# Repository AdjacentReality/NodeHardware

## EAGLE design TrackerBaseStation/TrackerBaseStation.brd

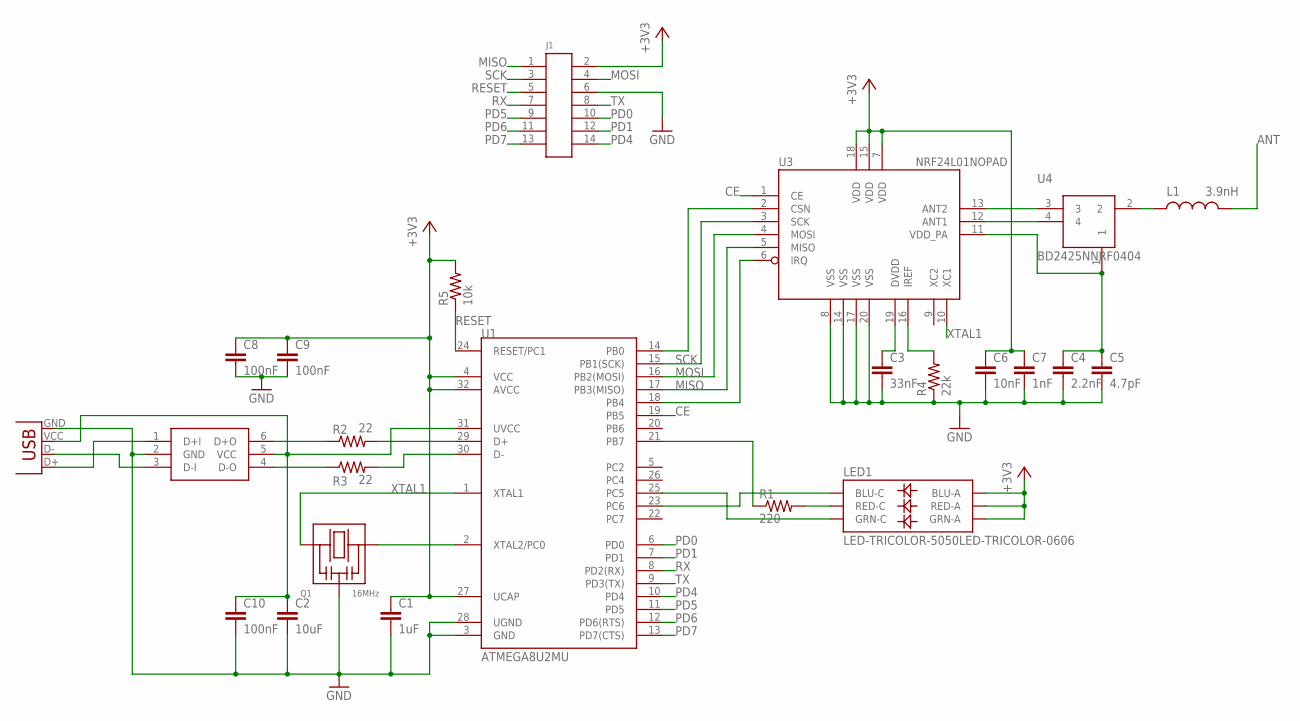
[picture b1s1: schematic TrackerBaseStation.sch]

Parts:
C1: 1uF; 0402-CAP
C2: 10uF; 0603-CAP
C3: 33nF; 0402-CAP
C4: 2.2nF; 0402-CAP
C5: 4.7pF; 0402-CAP
C6: 10nF; 0402-CAP
C7: 1nF; 0402-CAP
C8, C9, C10: 100nF; 0402-CAP
J1: DF12A3.0-14DS
L1: 3.9nH; C0402
LED1: LED-TRICOLOR-5050LED-TRICOLOR-0606; 0606
Q1: 16MHz; PRQC
R1: 220; 0402-RES
R2, R3: 22; 0402-RES
R4: 22k; 0402-RES
R5: 10k; 0402-RES
U1: ATMEGA8U2MU; QFN32
U2: RCLAMP0502A; SOT-666
U3: NRF24L01NOPAD; QFN20-NOPAD
U4: BD2425NNRF0404; BD2425NNRF
X1: USB-LEG; USB-A-SMD-LEG

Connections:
+3V3: C1.1, C6.1, C7.1, C8.1, C9.1, J1.2, LED1.4 (BLU-A), LED1.5 (RED-A), LED1.6 (GRN-A), R5.2, U1.4 (VCC), U1.27 (UCAP), U1.32 (AVCC), U3.7 (VDD), U3.15 (VDD), U3.18 (VDD)
ANT: L1.2
CE: U1.19 (PB5), U3.1 (CE)
GND: C1.2, C2.2, C3.2, C4.2, C5.2, C6.2, C7.2, C8.2, C9.2, C10.2, J1.6, Q1.P$2 (GND), R4.1, U1.3 (GND), U1.28 (UGND), U2.2 (GND), U3.8 (VSS), U3.14 (VSS), U3.17 (VSS), U3.20 (VSS), X1.GND
MISO: J1.1, U1.17 (PB3(MISO)), U3.5 (MISO)
MOSI: J1.4, U1.16 (PB2(MOSI)), U3.4 (MOSI)
unnamed: LED1.1 (BLU-C), U1.23 (PC6)
unnamed: LED1.2 (RED-C), R1.2
unnamed: R1.1, U1.21 (PB7)
unnamed: LED1.3 (GRN-C), U1.25 (PC5)
unnamed: Q1.P$3 (2), U1.2 (XTAL2/PC0)
unnamed: U2.3 (D-I), X1.D-
unnamed: U2.1 (D+I), X1.D+
unnamed: U1.14 (PB0), U3.2 (CSN)
unnamed: R2.1, U2.6 (D+O)
unnamed: R2.2, U1.29 (D+)
unnamed: R3.1, U2.4 (D-O)
unnamed: R3.2, U1.30 (D-)
unnamed: C2.1, C10.1, U1.31 (UVCC), U2.5 (VCC), X1.VCC (VBUS)
unnamed: U1.18 (PB4), U3.6 (IRQ)
unnamed: C3.1, U3.19 (DVDD)
unnamed: R4.2, U3.16 (IREF)
unnamed: U3.13 (ANT2), U4.3
unnamed: U3.12 (ANT1), U4.4
unnamed: L1.1, U4.2
unnamed: C4.1, C5.1, U3.11 (VDD_PA), U4.1
PD0: J1.10, U1.6 (PD0)
PD1: J1.12, U1.7 (PD1)
PD4: J1.14, U1.10 (PD4)
PD5: J1.9, U1.11 (PD5)
PD6: J1.11, U1.12 (PD6(RTS))
PD7: J1.13, U1.13 (PD7(CTS))
RESET: J1.5, R5.1, U1.24 (RESET/PC1)
RX: J1.7, U1.8 (PD2(RX))
SCK: J1.3, U1.15 (PB1(SCK)), U3.3 (SCK)
TX: J1.8, U1.9 (PD3(TX))
XTAL1: Q1.P$1 (1), U1.1 (XTAL1), U3.10 (XC1)

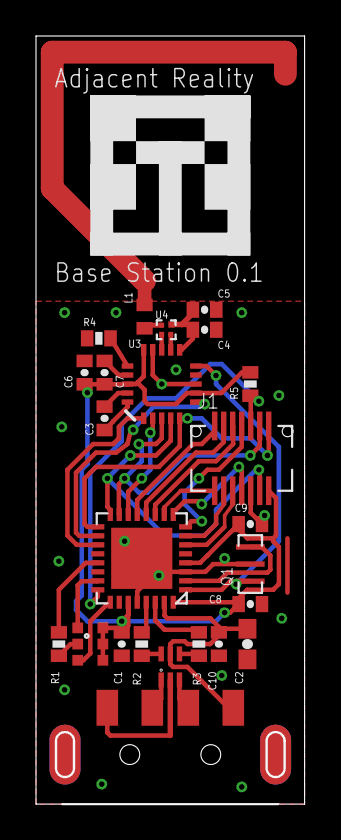
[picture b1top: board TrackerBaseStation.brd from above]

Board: 2 copper layers, 14.8 x 42.5 mm, 26 parts (1 on the bottom side), 36 nets.

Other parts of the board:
U$1: ADJACENTREALITY-LOGO-0.35
U$2: OSHW-LOGO-M

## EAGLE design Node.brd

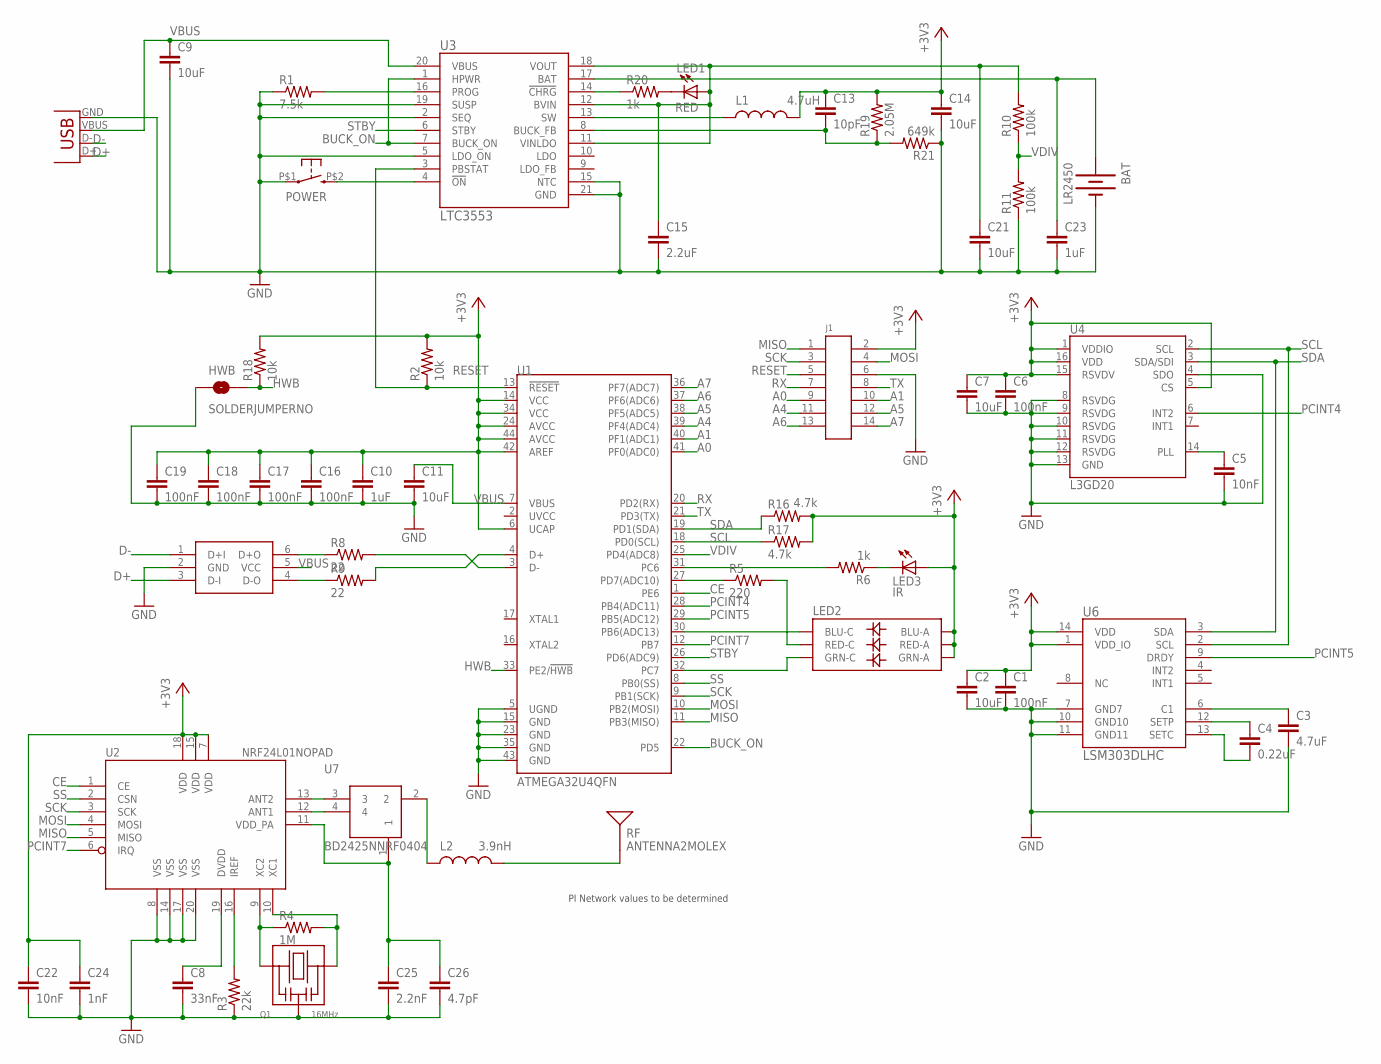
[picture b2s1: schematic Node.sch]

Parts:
BAT: LR2450; BATTCON_245MM_SLOT
C1, C6, C16, C17, C18, C19: 100nF; 0402-CAP
C2, C7, C9, C11, C14, C21: 10uF; 0603-CAP
C3: 4.7uF; 0603-CAP
C4: 0.22uF; 0402-CAP
C5, C22: 10nF; 0402-CAP
C8: 33nF; 0402-CAP
C10, C23: 1uF; 0402-CAP
C13: 10pF; 0402-CAP
C15: 2.2uF; 0402-CAP
C24: 1nF; 0402-CAP
C25: 2.2nF; 0402-CAP
C26: 4.7pF; 0402-CAP
HWB: SOLDERJUMPERNO; SJ_2S-NO
J1: DF12A3.0-14DS
L1: 4.7uH; VLS30
L2: 3.9nH; C0402
LED1: RED; LED-0603
LED2: LED-TRICOLOR-5050LED-TRICOLOR-0606; 0606
LED3: IR; LED-0603
POWER: KSS
Q1: 16MHz; PRQC
R1: 7.5k; 0402-RES
R2, R18: 10k; 0402-RES
R3: 22k; 0402-RES
R4: 1M; 0402-RES
R5: 220; 0402-RES
R6, R20: 1k; 0402-RES
R8, R9: 22; 0402-RES
R10, R11: 100k; 0402-RES
R16, R17: 4.7k; 0402-RES
R19: 2.05M; 0402-RES
R21: 649k; 0402-RES
RF: ANTENNA2MOLEX; MOLEX2.4SMD
U1: ATMEGA32U4QFN; QFN-44
U2: NRF24L01NOPAD; QFN20-NOPAD
U3: LTC3553; QFN20-3X3
U4: L3GD20; LGA16-4X4
U6: LSM303DLHC; LGA14-3X5
U7: BD2425NNRF0404; BD2425NNRF
U9: RCLAMP0502A; SOT-666
X1: USB-FCI; USB-MICROB-FCI

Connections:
+3V3: C1.1, C2.1, C6.1, C7.1, C10.1, C13.1, C14.1, C16.1, C17.1, C18.1, C19.1, C22.1, C24.1, J1.2, L1.2, LED2.4 (BLU-A), LED2.5 (RED-A), LED2.6 (GRN-A), LED3.A, R2.2, R16.2, R17.2, R18.2, R19.2, U1.6 (UCAP), U1.14 (VCC), U1.24 (AVCC), U1.34 (VCC), U1.42 (AREF), U1.44 (AVCC), U2.7 (VDD), U2.15 (VDD), U2.18 (VDD), U4.1 (VDDIO), U4.5 (CS), U4.15 (RSVDV), U4.16 (VDD), U6.1 (VDD_IO), U6.14 (VDD)
A0: J1.9, U1.41 (PF0(ADC0))
A1: J1.10, U1.40 (PF1(ADC1))
A4: J1.11, U1.39 (PF4(ADC4))
A5: J1.12, U1.38 (PF5(ADC5))
A6: J1.13, U1.37 (PF6(ADC6))
A7: J1.14, U1.36 (PF7(ADC7))
BUCK_ON: U1.22 (PD5), U3.1 (HPWR), U3.7 (BUCK_ON)
CE: U1.1 (PE6), U2.1 (CE)
D+: U9.3 (D-I), X1.D+
D-: U9.1 (D+I), X1.D-
GND: BAT.GND (-), C1.2, C2.2, C3.2, C5.2, C6.2, C7.2, C8.2, C9.2, C10.2, C11.2, C14.2, C15.2, C16.2, C17.2, C18.2, C19.2, C21.2, C22.2, C23.2, C24.2, C25.2, C26.2, HWB.1, J1.6, POWER.P$1 (1), Q1.P$2 (GND), R1.1, R3.1, R11.1, R21.1, U1.5 (UGND), U1.15 (GND), U1.23 (GND), U1.35 (GND), U1.43 (GND), U2.8 (VSS), U2.14 (VSS), U2.17 (VSS), U2.20 (VSS), U3.2 (SEQ), U3.5 (LDO_ON), U3.15 (NTC), U3.19 (SUSP), U3.21 (GND), U4.4 (SDO), U4.8 (RSVDG), U4.9 (RSVDG), U4.10 (RSVDG), U4.11 (RSVDG), U4.12 (RSVDG), U4.13 (GND), U6.7 (GND7), U6.10 (GND10), U6.11 (GND11), U9.2 (GND), X1.GND
HWB: HWB.2, R18.1, U1.33 (PE2/!HWB)
MISO: J1.1, U1.11 (PB3(MISO)), U2.5 (MISO)
MOSI: J1.4, U1.10 (PB2(MOSI)), U2.4 (MOSI)
unnamed: C15.1, C21.1, LED1.A, R10.2, U3.11 (VINLDO), U3.12 (BVIN), U3.18 (VOUT)
unnamed: R1.2, U3.16 (PROG)
unnamed: C3.1, U6.6 (C1)
unnamed: R6.2, U1.31 (PC6)
unnamed: C4.1, U6.12 (SETP)
unnamed: C4.2, U6.13 (SETC)
unnamed: C5.1, U4.14 (PLL)
unnamed: POWER.P$2 (3), U3.4 (!ON)
unnamed: LED2.2 (RED-C), R5.2
unnamed: LED3.C, R6.1
unnamed: C8.1, U2.19 (DVDD)
unnamed: LED2.3 (GRN-C), U1.32 (PC7)
unnamed: LED1.C, R20.2
unnamed: R3.2, U2.16 (IREF)
unnamed: R8.2, U1.3 (D-)
unnamed: R20.1, U3.14 (!CHRG)
unnamed: LED2.1 (BLU-C), U1.30 (PB6(ADC13))
unnamed: R5.1, U1.27 (PD7(ADC10))
unnamed: Q1.P$1 (1), R4.1, U2.9 (XC2)
unnamed: Q1.P$3 (2), R4.2, U2.10 (XC1)
unnamed: U2.13 (ANT2), U7.3
unnamed: U2.12 (ANT1), U7.4
unnamed: C25.1, C26.1, U2.11 (VDD_PA), U7.1
unnamed: R9.2, U1.4 (D+)
unnamed: R8.1, U9.6 (D+O)
unnamed: R9.1, U9.4 (D-O)
unnamed: L1.1, U3.13 (SW)
unnamed: L2.1, U7.2
unnamed: BAT.+1 (+), BAT.+2 (+), BAT.+3 (+), BAT.+4 (+), C23.1, U3.17 (BAT)
unnamed: L2.2, RF.FEED
unnamed: C13.2, R19.1, R21.2, U3.8 (BUCK_FB)
PCINT4: U1.28 (PB4(ADC11)), U4.6 (INT2)
PCINT5: U1.29 (PB5(ADC12)), U6.9 (DRDY)
PCINT7: U1.12 (PB7), U2.6 (IRQ)
RESET: J1.5, R2.1, U1.13 (!RESET), U3.3 (PBSTAT)
RX: J1.7, U1.20 (PD2(RX))
SCK: J1.3, U1.9 (PB1(SCK)), U2.3 (SCK)
SCL: R17.1, U1.18 (PD0(SCL)), U4.2 (SCL), U6.2 (SCL)
SDA: R16.1, U1.19 (PD1(SDA)), U4.3 (SDA/SDI), U6.3 (SDA)
SS: U1.8 (PB0(SS)), U2.2 (CSN)
STBY: U1.26 (PD6(ADC9)), U3.6 (STBY)
TX: J1.8, U1.21 (PD3(TX))
VBUS: C9.1, C11.1, U1.7 (VBUS), U3.20 (VBUS), U9.5 (VCC), X1.VBUS
VDIV: R10.1, R11.2, U1.25 (PD4(ADC8))

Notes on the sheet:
PI Network values to be determined

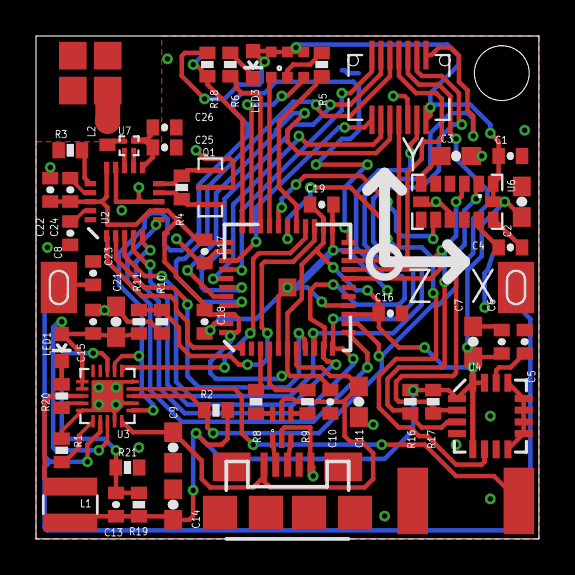
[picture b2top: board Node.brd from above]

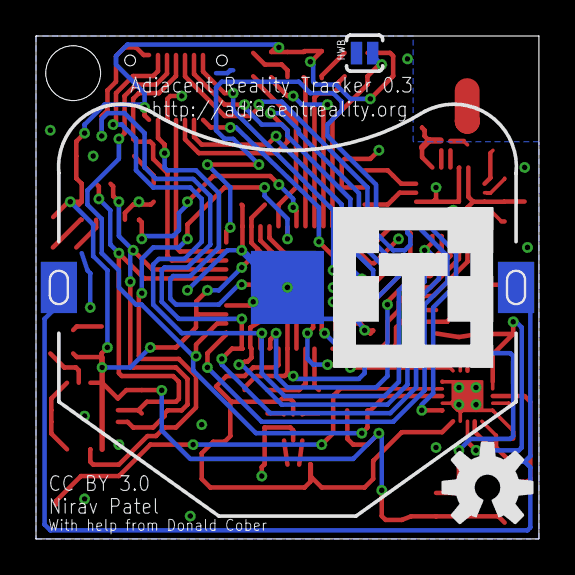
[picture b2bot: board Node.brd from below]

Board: 2 copper layers, 27.8 x 27.8 mm, 62 parts (4 on the bottom side), 59 nets.

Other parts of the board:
U$1: STAND-OFF-TIGHT
U$2: OSHW-LOGO-M
U$3: ADJACENTREALITY-LOGO-0.35

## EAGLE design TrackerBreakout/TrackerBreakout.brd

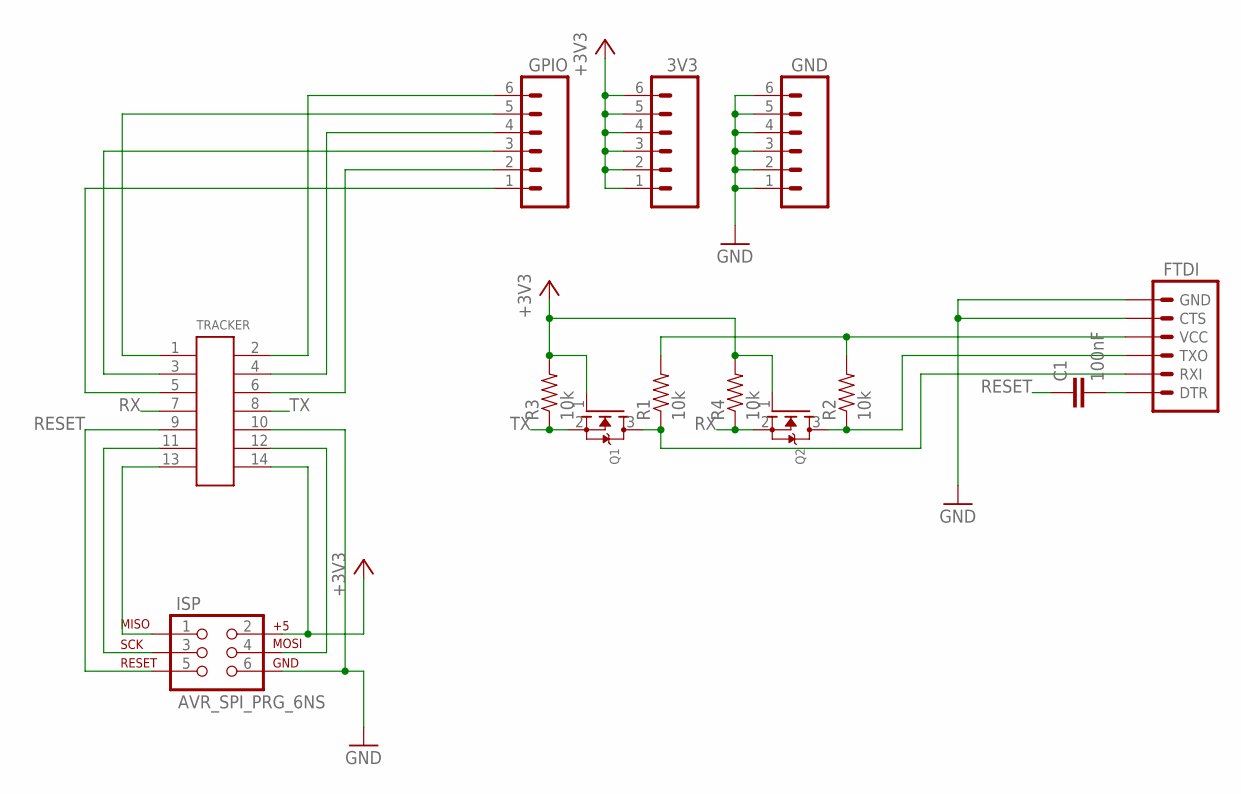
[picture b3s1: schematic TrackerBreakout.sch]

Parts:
3V3: M06SIP; 1X06
C1: 100nF; 0402-CAP
FTDI: ARDUINO_SERIAL_PROGRAMPTH; 1X06
GND: M06SIP; 1X06
GPIO: M06SIP; 1X06
ISP: AVR_SPI_PRG_6NS; 2X3-NS
Q1, Q2: MOSFET-N; SOT416
R1, R2, R3, R4: 10k; 0402-RES
TRACKER: DF12A3.0-14DS

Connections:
+3V3: 3V3.1, 3V3.2, 3V3.3, 3V3.4, 3V3.5, 3V3.6, ISP.2, Q1.1 (G), Q2.1 (G), R3.2, R4.2, TRACKER.14
GND: FTDI.5 (CTS), FTDI.6 (GND), GND.1, GND.2, GND.3, GND.4, GND.5, GND.6, ISP.6, TRACKER.10
unnamed: GPIO.1, TRACKER.5
unnamed: GPIO.2, TRACKER.6
unnamed: GPIO.3, TRACKER.3
unnamed: GPIO.4, TRACKER.4
unnamed: GPIO.5, TRACKER.1
unnamed: GPIO.6, TRACKER.2
unnamed: ISP.3, TRACKER.11
unnamed: ISP.4, TRACKER.12
unnamed: FTDI.4 (VCC), R1.2, R2.2
unnamed: ISP.1, TRACKER.13
unnamed: C1.2, FTDI.1 (DTR)
unnamed: FTDI.3 (TXO), Q2.3 (D), R2.1
unnamed: FTDI.2 (RXI), Q1.3 (D), R1.1
RESET: C1.1, ISP.5, TRACKER.9
RX: Q2.2 (S), R4.1, TRACKER.7
TX: Q1.2 (S), R3.1, TRACKER.8

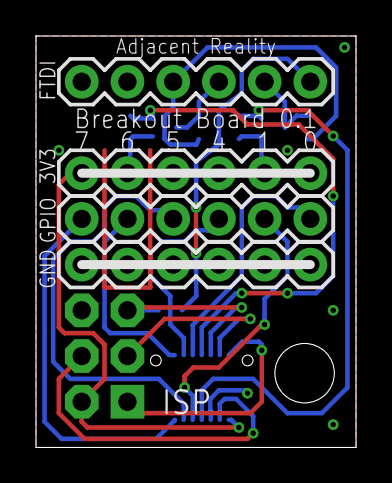
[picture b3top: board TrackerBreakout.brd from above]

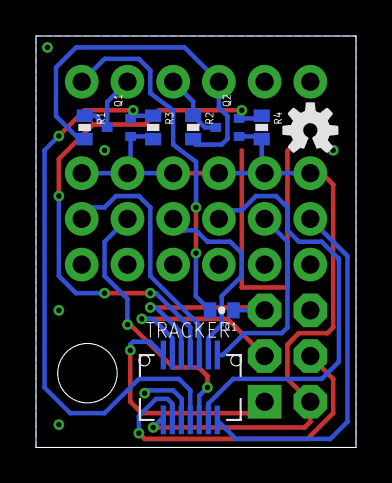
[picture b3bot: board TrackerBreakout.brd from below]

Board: 2 copper layers, 17.8 x 22.9 mm, 15 parts (9 on the bottom side), 18 nets.

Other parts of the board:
U$1: STAND-OFF
U$2: OSHW-LOGO-S

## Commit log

2012-02-13 Make a repository covering only Node hardware files
2012-04-12 starting rev 2, using LTC3554
2012-04-13 properly decouple LTC3554
2012-04-13 and one more 1uF for the battery
2012-04-13 add LSM303DLHC package
2012-04-14 swap 32u4 to tfqp, flip battery, LSM303DLHC
2012-04-14 add VLS30 inductor package
2012-04-14 add header for power button
2012-04-14 start of board layout
2012-04-14 it all sort of fits in the box
2012-04-14 mostly realistic parts placement
2012-04-14 pass ERC
2012-04-14 mostly pass DRC
2012-04-15 more routing
2012-04-15 route header
2012-04-15 mostly complete routing
2012-04-15 fix a bunch of tiny air wires
2012-04-15 one wire left
2012-04-15 the rats have flown the nest
2012-04-15 move the user button and stand-off
2012-04-15 labels on top layer
2012-04-15 nearly complete bottom silkscreen
2012-04-16 12mil ground pour isolation
2012-04-16 bottom layer silkscreen
2012-05-06 Created gh-pages branch via GitHub
2012-05-06 images of the tracker
2012-05-06 basic enclosure for Tracker 0.2
2012-05-07 improve case lid
2012-05-15 sphere and spray can cases
2012-05-16 fix spray can button shape
2012-06-10 sphere cutout
2012-06-10 cleanup for rev3 and use ltc3553
2012-06-15 add header and crystal
2012-06-16 balun for nrf24l01
2012-06-16 add the antenna
2012-06-16 cleanup some names
2012-06-17 start of base station
2012-06-18 usb port parts
2012-06-18 mostly complete base station
2012-06-18 pin header for base station
2012-06-18 breakout board schematic
2012-06-22 start of 0.3 layout
2012-06-24 start of base station layout
2012-06-24 with antenna
2012-06-24 silkscreen
2012-06-25 Breakout Board layout
2012-06-25 fix connector direction
2012-06-25 a few more painful wires
2012-06-25 so close
2012-06-26 the slow and steady march to zero airwires
2012-06-26 7 more to go
2012-06-26 all of the real airwires?
2012-06-26 with silkscreen
2012-07-20 fix capacitor size and nrf cream layer

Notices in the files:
Node.brd:
CC BY 3.0
TrackerBaseStation/TrackerBaseStation.brd:
Creative Commons By
parts and their libraries:
adjacent-reality: CC-BY-SA from SparkFun?
SparkFun: Licensing: CC v3.0 Share-Alike You are welcome to use this library for commercial purposes.
adjacent-reality: CC BY SA SparkFun
